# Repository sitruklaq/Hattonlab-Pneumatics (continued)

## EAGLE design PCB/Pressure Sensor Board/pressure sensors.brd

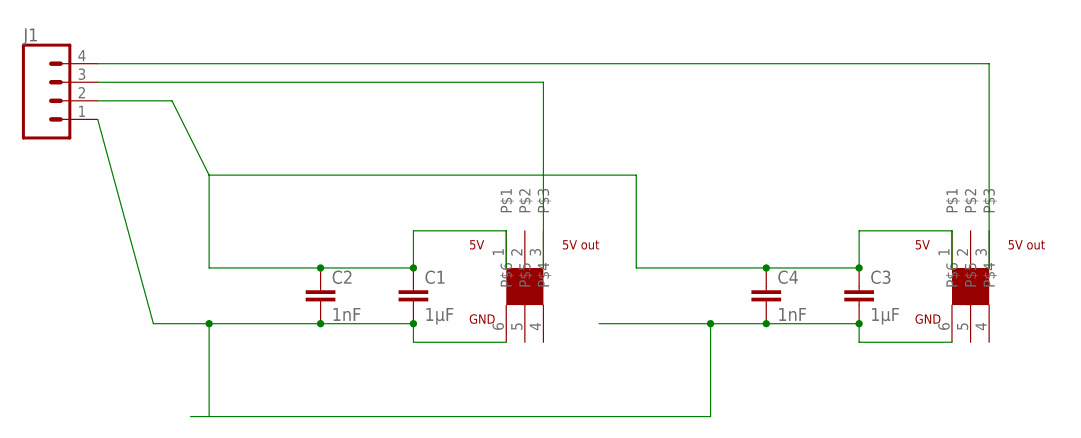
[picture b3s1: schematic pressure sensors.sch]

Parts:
C1, C3: 1µF; C050-030X075
C2, C4: 1nF; C050-030X075
J1: CONN_04; 1X04
U$1: 1; DIP750W53P254L720H850Q6B
U$2: ADP5101; DIP750W53P254L720H850Q6B

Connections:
5V: C1.1, C2.1, C3.1, C4.1, J1.2, U$1.1, U$2.1
GND: C1.2, C2.2, C3.2, C4.2, J1.1, U$1.6, U$2.6
unnamed: J1.3, U$1.3
unnamed: J1.4, U$2.3

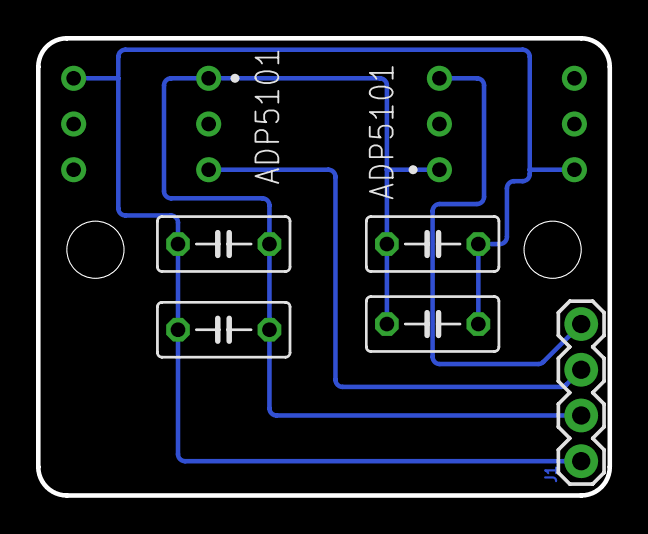
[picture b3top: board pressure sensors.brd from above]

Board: 2 copper layers, 31.8 x 25.4 mm, 7 parts (0 on the bottom side), 4 nets.

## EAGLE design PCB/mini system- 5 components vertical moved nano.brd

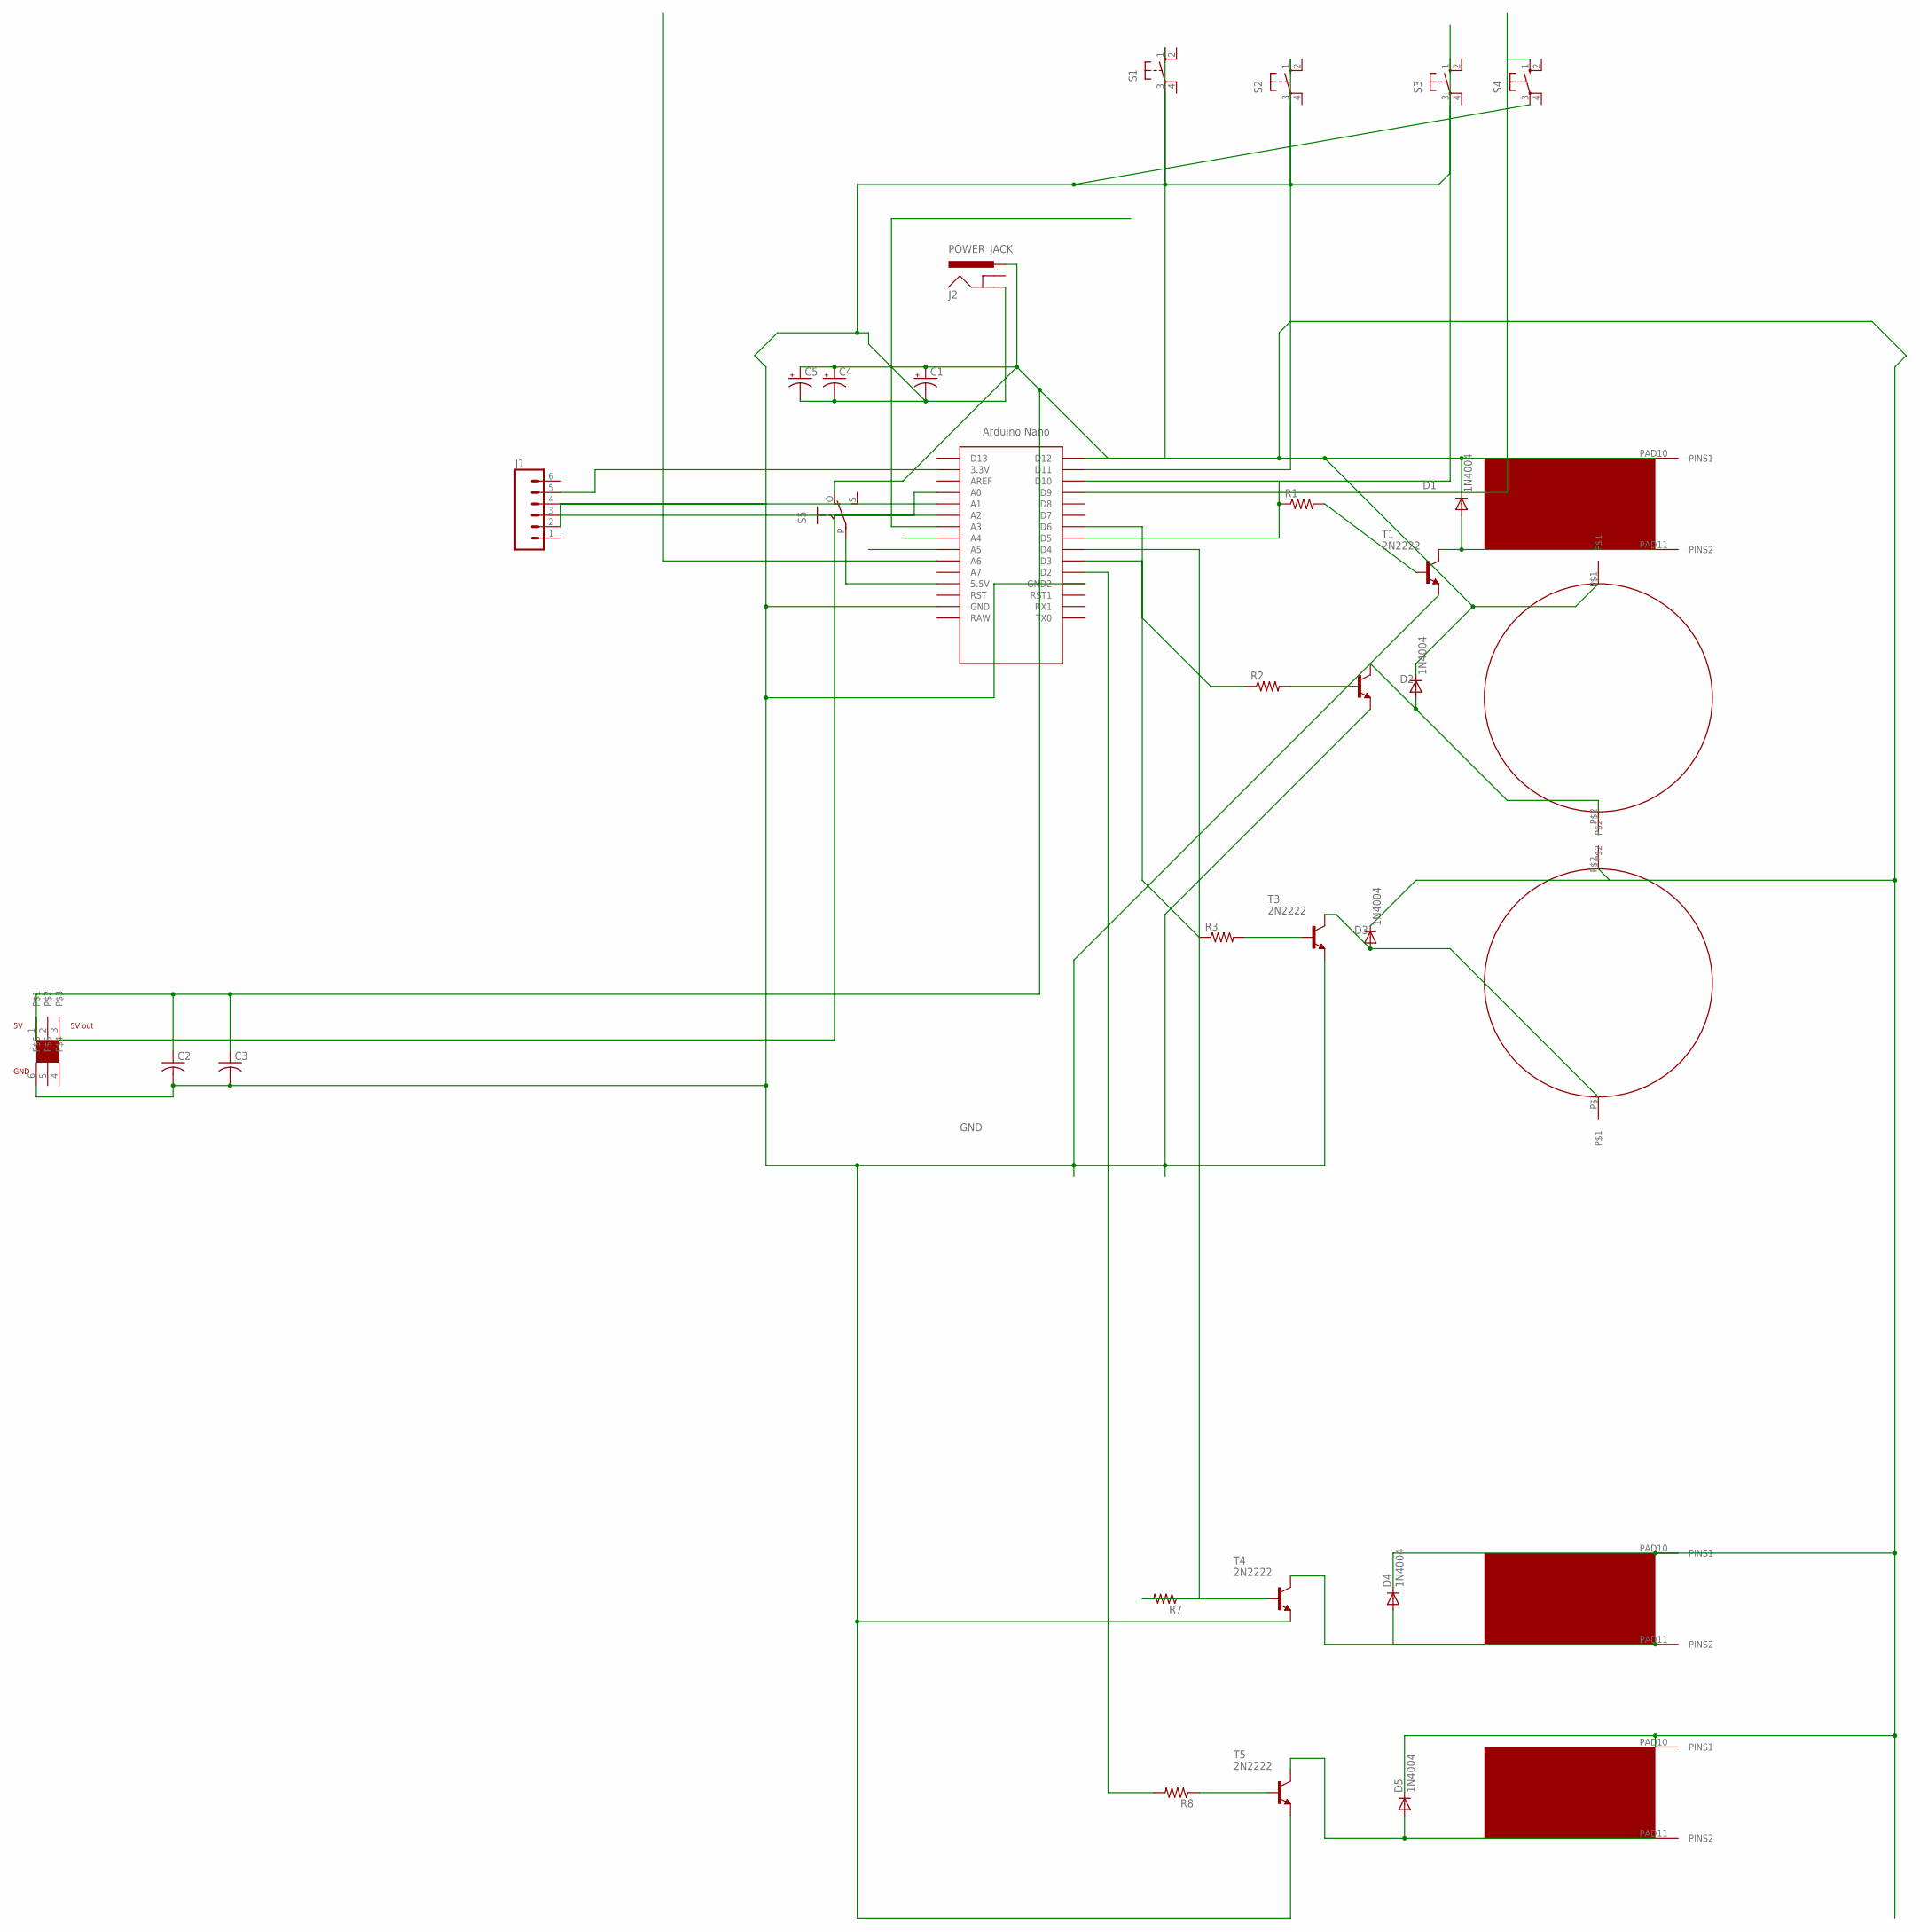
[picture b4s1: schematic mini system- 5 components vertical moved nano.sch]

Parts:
C1, C4: CPOL-USE2.5-5; E2,5-5
C2, C3: C-US025-024X044; C025-024X044
C5: CPOL-USE2.5-7; E2,5-7
D1, D2, D3, D4, D5: 1N4004; DO41-10
J1: CONN_06SILK_FEMALE_PTH; 1X06
J2: POWER_JACK; POWER_JACK_PTH
PUMP1: DCPUMP; PUMP
R1, R2, R3, R7, R8: R-US_0207/10; 0207/10
S1, S2, S3, S4: 10-XX; B3F-10XX
S5: EG1218S; EG1218
T1, T2, T3, T4, T5: 2N2222; TO92-EBC-OVAL
U$1: NANO
U$2, U$3, U$6: VALVE; VALVTEST2
U$4: DCPUMP; PUMP
U$7: ADP5101; DIP750W53P254L720H850Q6B

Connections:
5V: C1.+, C2.1, C3.1, C4.+, C5.+, D1.C, D2.C, D3.C, D4.C, D5.C, J2.PWR, PUMP1.P$1, S5.O, U$2.PAD10 (PINS1), U$3.PAD10 (PINS1), U$4.P$2, U$6.PAD10 (PINS1), U$7.1
GND: C1.-, C2.2, C3.2, C4.-, C5.-, J1.4, J2.GND, S1.3, S2.3, S3.3, S4.3, T1.E, T2.E, T3.E, T4.E, T5.E, U$1.GND, U$1.GND1 (GND2), U$7.6
unnamed: R1.2, T1.B
unnamed: R2.2, T2.B
unnamed: R3.2, T3.B
unnamed: R1.1, U$1.D5
unnamed: D2.A, PUMP1.P$2, T2.C
unnamed: R3.1, U$1.D6
unnamed: R2.1, U$1.D3
unnamed: D1.A, T1.C, U$2.PAD11 (PINS2)
unnamed: D3.A, T3.C, U$4.P$1
unnamed: R8.2, U$1.D2
unnamed: J1.5, U$1.3.3V
unnamed: J1.3, U$1.A0
unnamed: S5.P, U$1.5V (5.5V)
unnamed: J1.2, U$1.A1
unnamed: D4.A, T4.C, U$3.PAD11 (PINS2)
unnamed: R7.1, T4.B
unnamed: R7.2, U$1.D4
unnamed: R8.1, T5.B
unnamed: D5.A, T5.C, U$6.PAD11 (PINS2)
unnamed: U$1.A2, U$7.3
unnamed: S3.1 (S), U$1.D10
unnamed: S4.1 (S), U$1.D9
unnamed: S2.1 (S), U$1.D11
unnamed: S1.1 (S), U$1.D12

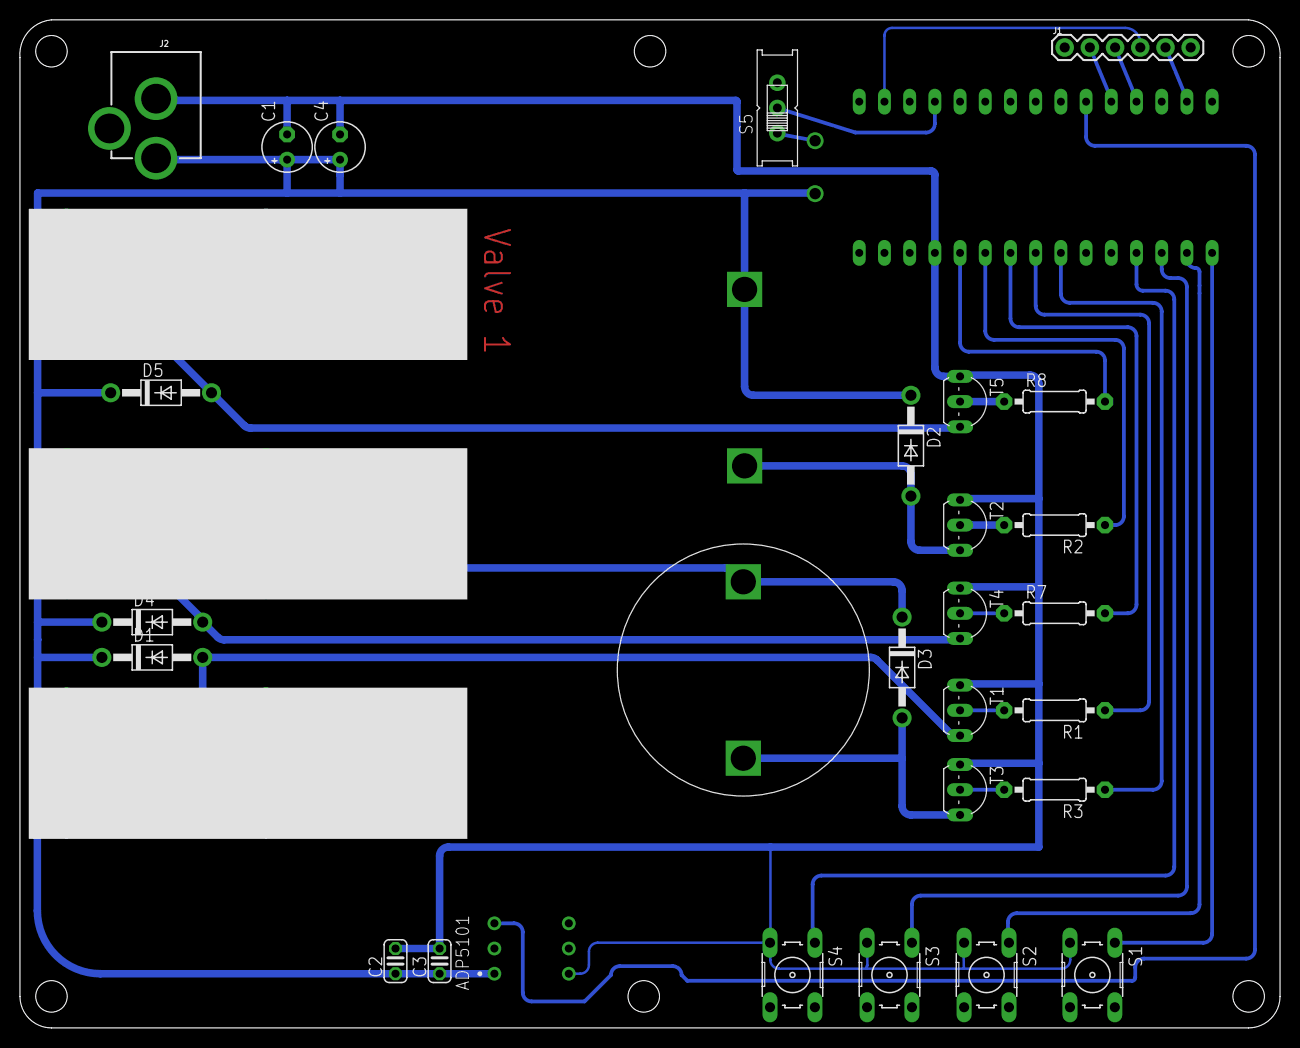
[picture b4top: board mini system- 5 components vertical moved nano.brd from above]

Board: 2 copper layers, 127.0 x 101.6 mm, 33 parts (1 on the bottom side), 26 nets.

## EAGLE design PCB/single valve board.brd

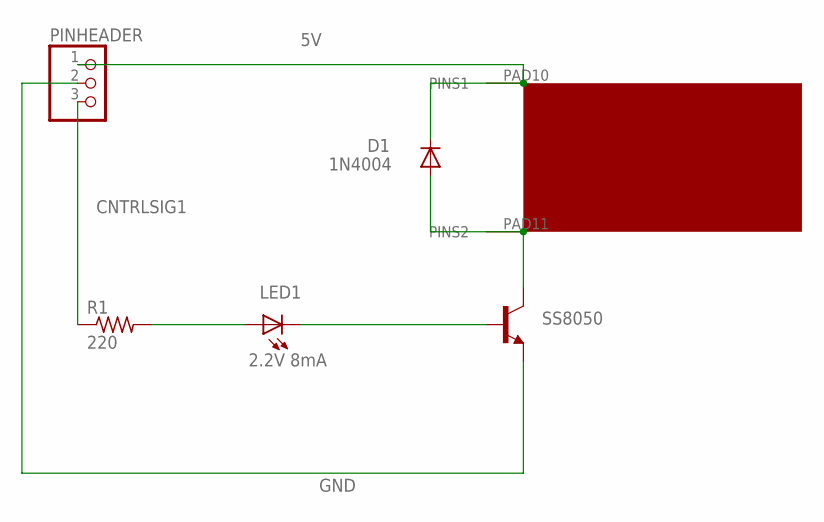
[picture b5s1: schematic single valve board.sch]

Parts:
D1: 1N4004; DO41-10
LED1: 2.2V 8mA; LED5MM
PINHEADER: PINHD-1X3; 1X03
R1: 220; 0207/10
SOLENOID1: SOLENOID1; VALVTEST2
SS8050: 2N2222; TO92-EBC-OVAL

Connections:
5V: D1.C, PINHEADER.1, SOLENOID1.PAD10 (PINS1)
CNTRLSIG1: PINHEADER.3, R1.1
GND: PINHEADER.2, SS8050.E
unnamed: D1.A, SOLENOID1.PAD11 (PINS2), SS8050.C
unnamed: LED1.K (C), SS8050.B
unnamed: LED1.A, R1.2

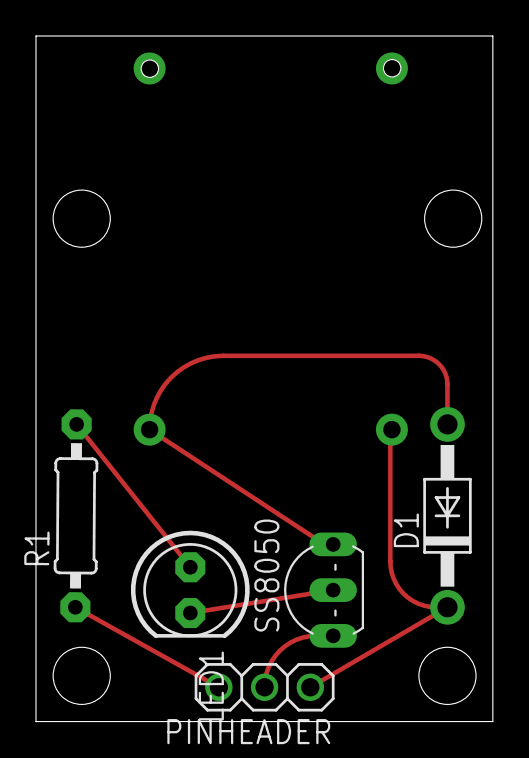
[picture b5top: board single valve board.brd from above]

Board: 2 copper layers, 25.4 x 38.1 mm, 6 parts (1 on the bottom side), 6 nets.

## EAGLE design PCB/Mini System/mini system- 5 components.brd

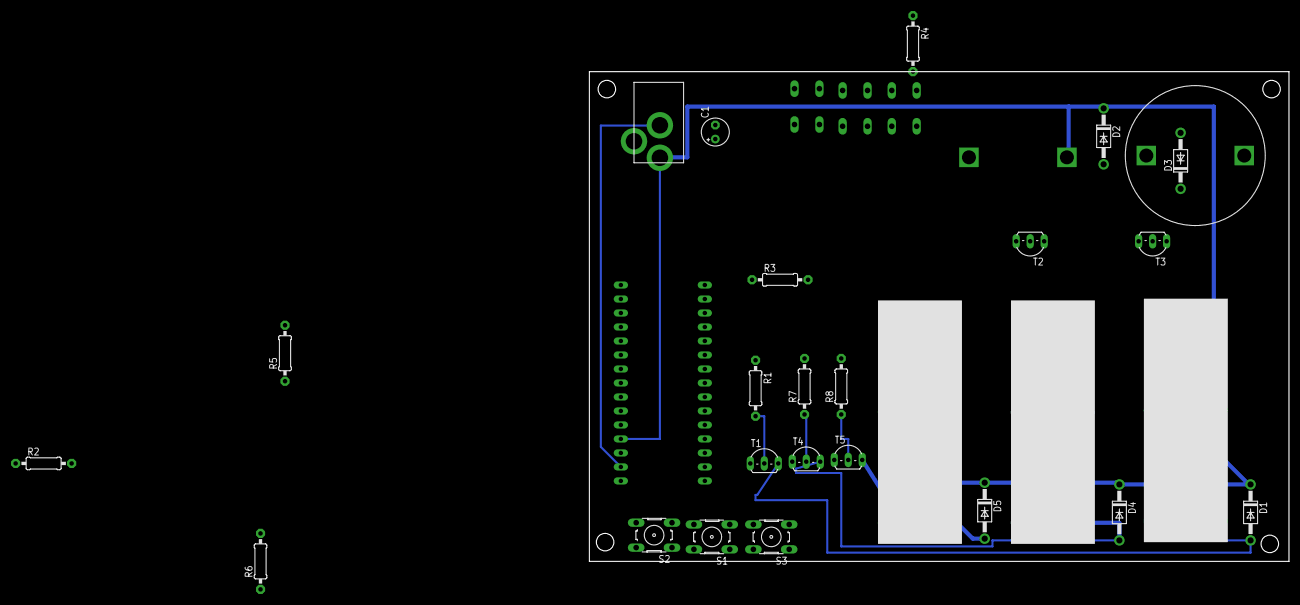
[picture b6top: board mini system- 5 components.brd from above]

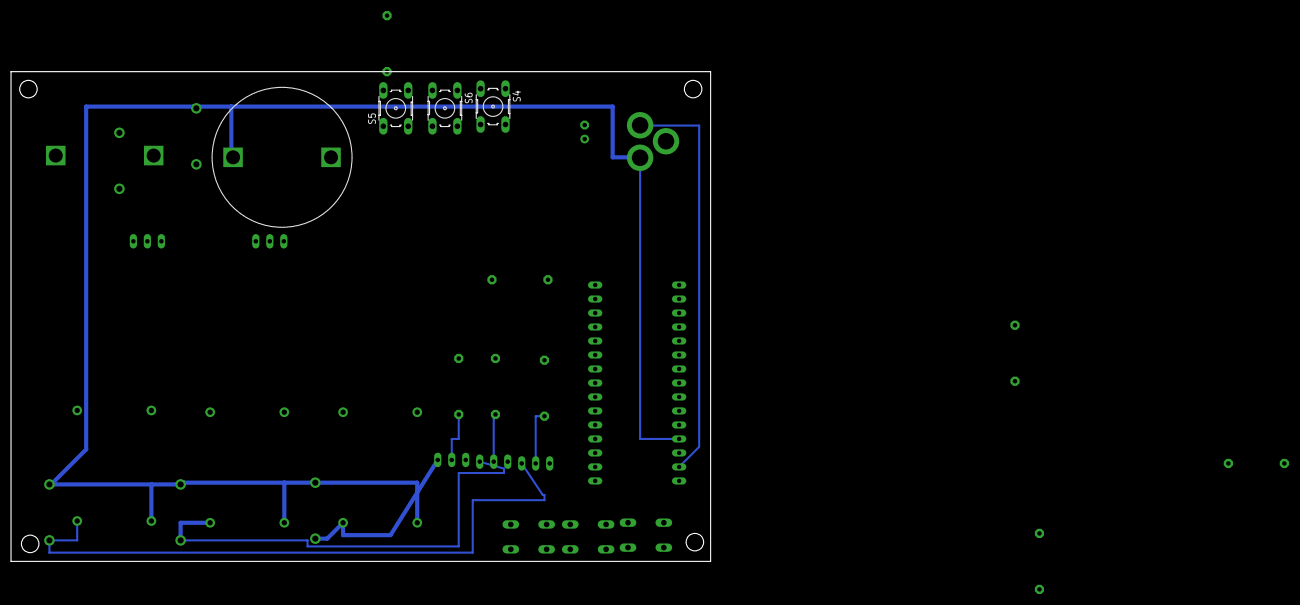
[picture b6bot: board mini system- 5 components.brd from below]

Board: 2 copper layers, 127.0 x 88.9 mm, 32 parts (4 on the bottom side), 23 nets.

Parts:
C1: E2,5-5
D1, D2, D3, D4, D5: 1N4004; DO41-10
PUMP1: DCPUMP; PUMP
R1, R2, R3, R4, R5, R6, R7, R8: 0207/10
S1, S2, S3, S4, S5, S6: B3F-10XX
T1, T2, T3, T4, T5: 2N2222; TO92-EBC-OVAL
U$1: NANO
U$2, U$3, U$6: VALVTEST2
U$4: DCPUMP; PUMP
U$5: 2.1MMJACKTHM; PJ-102A

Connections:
5V: C1.+, D1.C, D2.C, D3.C, D4.C, D5.C, PUMP1.P$1, S4.3, S5.1, S6.3, U$1.5V, U$2.PAD10, U$3.PAD10, U$4.P$2, U$5.TIP, U$6.PAD10
GND: C1.-, S1.3, S2.3, S3.3, T1.E, T2.E, T3.E, T4.E, T5.E, U$1.GND, U$5.RING
unnamed: R1.2, R6.2, T1.B
unnamed: R2.2, R4.1, T2.B
unnamed: R3.2, R5.2, T3.B
unnamed: R1.1, U$1.D2
unnamed: D2.A, PUMP1.P$2, T2.C
unnamed: R3.1, U$1.D5
unnamed: R2.1, U$1.D6
unnamed: D1.A, T1.C, U$2.PAD11
unnamed: D3.A, T3.C, U$4.P$1
unnamed: R4.2, S5.3
unnamed: S1.1, U$1.D11
unnamed: S2.1, U$1.D10
unnamed: S3.1, U$1.D12
unnamed: R6.1, S6.1, S6.2
unnamed: R5.1, S4.1
unnamed: D4.A, T4.C, U$3.PAD11
unnamed: R7.1, T4.B
unnamed: R7.2, U$1.D3
unnamed: R8.2, U$1.D4
unnamed: R8.1, T5.B
unnamed: D5.A, T5.C, U$6.PAD11

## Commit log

2018-12-08 initialization of the project
2018-12-10 pcb boards and cad
2018-12-10 update board
2018-12-10 board update
2018-12-14 pressure sensor board update
2018-12-15 board updates
2018-12-15 update psensor
2018-12-15 increased hole size for pressure sensor
2018-12-15 sensors agin
2018-12-15 push
2018-12-16 4 valve boards
2019-01-18 mini system board
2019-01-18 new board
2019-01-27 new mini system
2019-05-16 added new arduino code and matlab scripts
2019-05-27 test data May 27
2019-06-07 pos-pressure
2019-07-03 new stuff
2019-07-03 new data
2019-09-09 add contact swithcing
2020-01-21 updated BOM
2020-01-21 added images of setup
2020-01-21 moved BOM to components
2020-01-24 update arduino code and add matlab program
2020-01-24 update arduino code
2020-01-24 Created Arduino Serial Command List
2020-01-25 Update Arduino Command List
2020-01-25 added checklist for visual code
2020-01-25 added GUI readme
2020-01-25 added more to todo
2020-01-25 Added Images of PCBs and sorted
2020-03-26 added files
2021-02-08 Fixed labeling of 5V and GND inputs
